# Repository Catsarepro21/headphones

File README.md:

# Headphones

I wanted to make my own over-ear headphones and learn how to fit the audio electronics, battery, and controls into something I could actually wear. I also wanted a fold-up mic and RGB around the cups.

The cups are closed-back and use 40 mm Dayton drivers, an adjustable OKCSC headband, and Brainwavz memory-foam pads. There are 16 LEDs in each cup. The design uses Bluetooth for phone audio, a USB dongle for PC audio and the boom mic, and USB-C for charging and wired SignalRGB. The first physical build still needs testing.

## PCB and schematic

## Files

- [BOM](BOM.md) and [CSV](BOM.csv)
- [Onshape assembly](https://cad.onshape.com/documents/7dd0dda11718de6338e637f2/w/5f67542aa0c734a01c21f813/e/294b57f9c610073ea687bedc) and [STEP files](CAD/)
- [KiCad projects and fabrication files](PCB/fabrication/)
- [Wiring](https://github.com/Catsarepro21/headphones/blob/79efcd8d71c05d15650749ef6cd352ed8c2b8722/PCB/Harness%20wiring.md) and [RGB power](https://github.com/Catsarepro21/headphones/blob/79efcd8d71c05d15650749ef6cd352ed8c2b8722/PCB/LED%20rail%20protection.md)
- [Headset firmware](code/headset/) and [dongle firmware](code/dongle/)
- [SignalRGB plugin](code/signalrgb/Headphones.js)

## How to build it

1. Order the boards from the [fabrication folders](PCB/fabrication/). You need one of each board and two copies of the RGB ring. Check the board thicknesses before ordering.
2. Print the parts from [Onshape](https://cad.onshape.com/documents/7dd0dda11718de6338e637f2/w/5f67542aa0c734a01c21f813/e/294b57f9c610073ea687bedc). Dry-fit the headband, pads, baffles, and battery wiring before committing to the final cup prints. The deeper baffles still need a fit check with the actual battery and thermistor.
3. Solder the boards and run the wires using the [pinout](https://github.com/Catsarepro21/headphones/blob/79efcd8d71c05d15650749ef6cd352ed8c2b8722/PCB/Harness%20wiring.md). The main board has a few parts to leave off, so check the [assembly notes](https://github.com/Catsarepro21/headphones/blob/79efcd8d71c05d15650749ef6cd352ed8c2b8722/PCB/fabrication/README.md#before-assembly) first. Try the BM83 soldering setup on a spare board.
4. Check for shorts and confirm battery polarity before plugging anything in. Start with a current-limited supply and leave the battery and RGB rings disconnected.
5. Flash the [headset](code/headset/) and [dongle](code/dongle/) over SWD. Measure the dongle's reference voltage first and use a probe that supports 1.8 V.
6. Try audio and the flip-up mic in both modes, then check charging and RGB. Make sure your ears clear the grilles when the pads compress before closing up the cups.

## BOM

One build comes to about **$309.35**, including $25 for printing and its shipping and $3 for the selector seal. If you need calipers, add $11.99 for a **$321.34** total. Other shipping, tax, and extra bench tools are separate. [Caliper](https://www.harborfreight.com/painting/measuring-marking/calipers-micrometer/6-in-composite-digital-caliper-63586.html) [Pricing sheet](https://docs.google.com/spreadsheets/d/1EZlvAER-2UgOb8yQGnecRwhJc7PUS93z2gQPCFvvkVY/edit)

| Item | Quantity | Description | Link | Unit price (USD) | Total price (USD) | Notes |
| --- | --- | --- | --- | --- | --- | --- |
| OKCSC 110 mm padded headband | 1 | Adjustable headband and yokes | [Buy](<https://www.aliexpress.us/item/3256810368016901.html>) | $29.00 | $29.00 | 110 mm variant. |
| Brainwavz Oval Micro Suede BWAVZ-OVLBKMS-BAR | 1 | Black foam pair. 110 × 90 × 30 mm, 70 × 50 mm opening. | [Buy](<https://www.brainwavzaudio.com/collections/accessories/products/headphone-memory-foam-earpads-oval-micro-suede>) | $18.55 | $18.55 | Rear mounting flap. |
| Dayton CE38MB-32 drivers | 2 | 40 mm nominal, 32 Ω each | [Buy](<https://www.parts-express.com/Dayton-Audio-CE38MB-32-1-1-2-Mini-Speaker-Black-32-Ohm-285-131>) | $3.49 | $6.98 | Sold individually. |
| Ebyte E73-2G4M08S1C | 2 | 2.4 GHz nRF52840 radio and MCU | [Buy](<https://www.robotshop.com/products/ebyte-e73-2g4m08s1c-iot-solutions-modules-nrf52840-ble50-smd-24ghz-nordic-wireless-module>) | $6.50 | $13.00 | One per board. |
| Microchip BM83SM1-00AB | 1 | Bluetooth Classic and headphone driver | [Buy](<https://www.digikey.com/en/products/detail/microchip-technology/BM83SM1-00AB/12823501>) | $13.18 | $13.18 |  |
| TI TLV320AIC3204IRHBR | 1 | Stereo codec with headphone amplifier | [Buy](<https://www.digikey.com/en/products/detail/texas-instruments/TLV320AIC3204IRHBR/1952545>) | $5.59 | $5.59 |  |
| TI TS5A22362DGSR | 3 | Speaker and mic/bias selection | [Buy](<https://www.lcsc.com/product-detail/Analog-Switches-Multiplexers_Texas-Instruments-TS5A22362DGSR_C201663.html>) | $0.9538 | $2.86 | LCSC part C201663. |
| PUI AOM-4544P-2-R capsules | 2 | One boom mic and one ambient mic | [Buy](<https://www.digikey.com/en/products/detail/pui-audio-inc/AOM-4544P-2-R/1745492>) | $1.48 | $2.96 | One capsule per mic. |
| TI BQ24074RGTR | 1 | 1S 4.20 V charger and power path | [Buy](<https://www.digikey.com/en/products/detail/texas-instruments/BQ24074RGTR/2047269>) | $2.43 | $2.43 | About 500 mA charge. USB starts at 100 mA, then about 390 mA after setup. |
| TI TPS63031DSKR | 1 | 3.3 V buck-boost supply | [Buy](<https://www.lcsc.com/product-detail/dc-dc-converters_texas-instruments-tps63031dskr_C15516.html>) | $1.0429 | $1.04 | LCSC part C15516. |
| Adafruit 2011 protected 1S pack | 1 | 2000 mAh, 3.7 V, 60 × 36 × 7 mm | [Buy](<https://www.digikey.com/en/products/detail/adafruit-industries-llc/2011/6612469>) | $12.50 | $12.50 | Battery for this build. Tray fit pending. |
| Semitec 103AT-2 thermistor | 1 | 10 kΩ at 25 °C, B3435 NTC for charger TS | [Buy](<https://www.digikey.com/en/products/detail/semitec-usa-corp/103at-2/16579059>) | $0.68 | $0.68 | External battery temperature sensor. |
| Adafruit 3814 battery pigtail | 1 | 2-pin JST-PH mating adapter for the 2011 | [Buy](<https://www.digikey.com/en/products/detail/adafruit-industries-llc/3814/9380221>) | $0.75 | $0.75 | Mates with the battery’s original plug. |
| TI TPS61023DRLR | 1 | 5 V boost for both RGB rings | [Buy](<https://www.digikey.com/en/products/detail/texas-instruments/TPS61023DRLR/11310629>) | $1.38 | $1.38 | U5 makes 5 V for the rings. 300 mA LED budget. |
| TI TPS2553DBVR-1 | 1 | U13 hardware cutoff for both LED rings | [Buy](<https://www.digikey.com/en/products/detail/texas-instruments/TPS2553DBVR-1/2047901>) | $1.06 | $1.06 | -1 latch-off version, SOT-23-6. R210 sets the limit. |
| 68.1 kΩ 0603 · Yageo RC0603FR-0768K1L | 1 | R210 sets the LED cutoff threshold | [Buy](<https://www.digikey.com/en/products/detail/yageo/RC0603FR-0768K1L/727354>) | $0.10 | $0.10 | 1%. Expected trip at 0.34–0.44 A. |
| TI SN74AHCT1G125DBVR | 1 | 3.3 V to 5 V RGB data buffer | [Buy](<https://www.digikey.com/en/products/detail/texas-instruments/SN74AHCT1G125DBVR/376028>) | $0.14 | $0.14 |  |
| TI TLV803EA29DBZR | 1 | BM83 2.93 V open-drain reset supervisor | [Buy](<https://www.digikey.com/en/products/detail/texas-instruments/TLV803EA29DBZR/11308855>) | $0.50 | $0.50 |  |
| Bourns SRN4018-1R5Y | 1 | 1.5 µH inductor for 3.3 V supply | [Buy](<https://www.digikey.com/en/products/detail/bourns-inc/SRN4018-1R5Y/3821618>) | $0.37 | $0.37 |  |
| Bourns SRN6045TA-1R0Y | 1 | 1.0 µH inductor for 5 V boost | [Buy](<https://www.digikey.com/en/products/detail/bourns-inc/SRN6045TA-1R0Y/6155099>) | $0.46 | $0.46 |  |
| Kyocera KC3225K12.2880C1GE00 | 1 | 12.288 MHz, 3.3 V codec master clock (Y1) | [Buy](<https://www.digikey.com/en/products/detail/kyocera-avx/KC3225K12-2880C1GE00/5322447>) | $1.39 | $1.39 | Cut tape. C212 bypass. |
| Amphenol 12401610E4#2A | 1 | USB-C headset receptacle | [Buy](<https://www.digikey.com/en/products/detail/amphenol-icc-commercial-products/12401610E4-2A/5775520>) | $1.43 | $1.43 |  |
| ST USBLC6-2SC6 | 1 | Headset USB data ESD array | [Buy](<https://www.digikey.com/en/products/detail/stmicroelectronics/USBLC6-2SC6/1040559>) | $0.54 | $0.54 |  |
| Nexperia PESD5V0U2BT-QR | 1 | Dongle USB D+ and D− ESD protection | [Buy](<https://www.digikey.com/en/products/detail/nexperia-usa-inc/PESD5V0U2BT-QR/17296191>) | $0.31 | $0.31 | Dongle D1 goes on the bottom (SOT-23). |
| Molex 1054440011 | 1 | Right-angle USB-C dongle plug | [Buy](<https://www.digikey.com/en/products/detail/molex/1054440011/6173183>) | $3.10 | $3.10 |  |
| Amphenol 10165794-Z0100YBLF USB-C cable | 1 | 1 m black USB-C to USB-C. USB 2.0 data and 5 V charging. | [Buy](<https://www.digikey.com/en/products/detail/amphenol-cs-fci/10165794-Z0100YBLF/22527932>) | $4.67 | $4.67 | Max plug body is 11.2 × 6.7 mm. Fits the 14.5 × 8.0 mm CAD opening. |
| Worldsemi WS2812B-B/W | 35 | Buy 35 to populate 32 pixels | [Buy](<https://www.lcsc.com/product-detail/C114586.html>) | $0.1042 | $3.65 | 32 LEDs used, 3 spare. |
| E-Switch TL3342F260QG | 5 | Four earcup controls and one main board reset switch | [Buy](<https://www.digikey.com/en/products/detail/e-switch/TL3342F260QG/6596498>) | $0.62 | $3.10 | Play/pause, volume +/−, pair, and mainboard reset. |
| C&K JS102011SAQN | 1 | Two-position Bluetooth/dongle selector | [Buy](<https://www.digikey.com/en/products/detail/c-k/JS102011SAQN/1640095>) | $0.90 | $0.90 | 2 mm travel. 1.0 mm selector PCB. |
| C&K 1101M1S3ZQE2 master power switch | 1 | Maintained slide switch connects main SW1 VSYS to SYS_SW | [Buy](<https://www.digikey.com/en/products/detail/c-k/1101M1S3ZQE2/67048>) | $8.05 | $8.05 | 6 A resistive at 28 VDC. Onshape M1. |
| Aratas / Omron B3F-1000 boom mute switch | 1 | 6 × 6 mm normally-open through-hole tact. Boom cam holds contact closed when deployed. | [Buy](<https://www.digikey.com/en/products/detail/aratas-formerly-omron-components/B3F-1000/33150>) | $0.35 | $0.35 | Mute switch on SW7 pads 1–2. Boom mic on J7. |
| Sullins PEC36SAAN 2.54 mm headers | 1 | 36-pin breakaway strip for the service headers | [Buy](<https://www.digikey.com/en/products/detail/sullins-connector-solutions/PEC36SAAN/859153>) | $1.44 | $1.44 | 8 pins used for J2 and J4. |
| Adafruit 5087 3-pin inline disconnect | 1 | Matched JST-PH-compatible 26 AWG pigtail pair | [Buy](<https://www.digikey.com/en/products/detail/adafruit-industries-llc/5087/14652853>) | $0.95 | $0.95 | Matched pair for the battery and temp sensor. |
| Qualtek Q2-Z-RK1-3/32-01-6IN-32 | 1 | 3/32 in black 2:1 heat shrink | [Buy](<https://www.digikey.com/en/products/detail/qualtek/Q2-Z-RK1-3-32-01-6IN-32/1210238>) | $1.38 | $1.38 | For small splices. |
| Qualtek Q2-Z-RK1-1/8-01-6IN-28 | 1 | 1/8 in black 2:1 heat shrink | [Buy](<https://www.digikey.com/en/products/detail/qualtek/Q2-Z-RK1-1-8-01-6IN-28/1210237>) | $1.52 | $1.52 | For thicker splices. |
| Qualtek Q2-Z-RK1-3/16-01-6IN-24 | 1 | 3/16 in black 2:1 heat shrink | [Buy](<https://www.digikey.com/en/products/detail/qualtek/Q2-Z-RK1-3-16-01-6IN-24/1210246>) | $1.59 | $1.59 | For larger lugs. |
| Adafruit 3892 flexible headband wire | 3 | Black stranded silicone 26 AWG. Each pack has four separate 1 m conductors. | [Buy](<https://www.digikey.com/en/products/detail/adafruit-industries-llc/3892/9603618>) | $1.95 | $5.85 | 9 wires through the headband. Ø1.5 ±0.1 mm each. |
| Lite-On LTST-C170KGKT | 1 | Dongle status indication | [Buy](<https://www.digikey.com/en/products/detail/liteon/LTST-C170KGKT/386776>) | $0.19 | $0.19 |  |
| 100 nF 0805 · Würth 885012207098R | 50 | Bypass | [Buy](<https://www.digikey.com/en/products/detail/w%C3%BCrth-elektronik/885012207098R/21719484>) | $0.0302 | $1.51 | 49 used. |
| 100 pF 0805 · KEMET C0805C101J5GACTU | 2 | Capacitors C27 and C29 | [Buy](<https://www.digikey.com/en/products/detail/kemet/C0805C101J5GACTU/411397>) | $0.19 | $0.38 | C0G, 50 V, ±5%. |
| 220 pF 0805 · KEMET C0805C221J5GACTU | 1 | Feed-forward capacitor across the RGB boost feedback upper resistor | [Buy](<https://www.digikey.com/en/products/detail/kemet/C0805C221J5GACTU/411402>) | $0.20 | $0.20 | C31. C0G, 50 V, ±5%. |
| 1 µF 0805 · Samsung CL21B105KOFNFNE | 10 | Coupling and bypass | [Buy](<https://www.digikey.com/en/products/detail/samsung-electro-mechanics/CL21B105KOFNFNE/3891016>) | $0.0590 | $0.59 | 7 used, 3 spare. |
| Murata GRM1885C1H103JA01J | 1 | 10 nF C0G 0603 bypass for the 12.288 MHz clock | [Buy](<https://www.digikey.com/en/products/detail/murata-electronics/GRM1885C1H103JA01J/4905215>) | $0.1300 | $0.13 | Main C212 next to Y1. 50 V, ±5%. |
| 1 µF 0603 · Yageo CC0603KRX7R7BB105 | 2 | C211 BM83 mic-bias bypass and C213 LED protection switch bypass | [Buy](<https://www.digikey.com/en/products/detail/yageo/CC0603KRX7R7BB105/2833611>) | $0.24 | $0.48 | X7R, 16 V, ±10%, 0603. |
| 4.7 µF 0805 · Samsung CL21B475KAFNNNE | 2 | Main charger input and dongle USB VBUS/VDDH bypass | [Buy](<https://www.digikey.com/en/products/detail/samsung-electro-mechanics/CL21B475KAFNNNE/3888627>) | $0.50 | $1.00 | 25 V X7R. Main C1 and dongle C1. |
| 10 µF 0805 · Samsung CL21B106KOQNNNE | 13 | Supply bypass and stabilization, 12 main and one dongle | [Buy](<https://www.digikey.com/en/products/detail/samsung-electro-mechanics/CL21B106KOQNNNE/3890958>) | $0.165 | $2.15 | Dongle C2 on VDD. X7R, 16 V, ±10%, 1.40 mm max. |
| 22 µF 0805 · Samsung CL21A226MPQNNNE | 3 | Boost and BM83 supply bypass | [Buy](<https://www.digikey.com/en/products/detail/samsung-electro-mechanics/CL21A226MPQNNNE/3888568>) | $0.19 | $0.57 | 10 V X5R. |
| 47 µF · Nichicon UWT1V470MCL1GS | 2 | One bulk capacitor on each LED ring | [Buy](<https://www.digikey.com/en/products/detail/nichicon/UWT1V470MCL1GS/589943>) | $0.44 | $0.88 | One C52 per ring. 35 V, ±20%, Ø6.3 × 5.8 mm. |
| 220 µF · Nichicon UWT0J221MCL6GS | 2 | Codec headphone DC blocking | [Buy](<https://www.digikey.com/en/products/detail/nichicon/UWT0J221MCL6GS/2550846>) | $0.39 | $0.78 | C24, C25. |
| 33 Ω 0805 · RC0805FR-0733RL | 10 | RGB/UART series | [Buy](<https://www.digikey.com/en/products/detail/yageo/RC0805FR-0733RL/730809>) | $0.0340 | $0.34 | 5 used. |
| 330 Ω 0805 · RC0805FR-07330RL | 2 | RGB data series | [Buy](<https://www.digikey.com/en/products/detail/yageo/RC0805FR-07330RL/727866>) | $0.10 | $0.20 |  |
| 1 kΩ 0805 · RC0805FR-071KL | 1 | Dongle status LED | [Buy](<https://www.digikey.com/en/products/detail/yageo/RC0805FR-071KL/727444>) | $0.10 | $0.10 | Dongle R5. |
| 1.78 kΩ 0805 · CRCW08051K78FKEA | 1 | Charge programming | [Buy](<https://www.digikey.com/en/products/detail/vishay-dale/CRCW08051K78FKEA/1175663>) | $0.10 | $0.10 | R1. |
| 2.2 kΩ 0805 · RC0805FR-072K2L | 2 | Electret bias | [Buy](<https://www.digikey.com/en/products/detail/yageo/RC0805FR-072K2L/727676>) | $0.10 | $0.20 | R18 and R19. |
| 3.92 kΩ 0805 · RC0805FR-073K92L | 1 | Main R2 charger input-current limit | [Buy](<https://www.digikey.com/en/products/detail/yageo/RC0805FR-073K92L/727840>) | $0.10 | $0.10 | 1%. Sets the configured USB input limit. R1 sets charge current. |
| 4.7 kΩ 0805 · RC0805FR-074K7L | 3 | Digital pull-up and bias | [Buy](<https://www.digikey.com/en/products/detail/yageo/RC0805FR-074K7L/727929>) | $0.10 | $0.30 |  |
| 5.1 kΩ 0805 · CRCW08055K10FKEA | 3 | USB-C CC terminations | [Buy](<https://www.digikey.com/en/products/detail/vishay-dale/CRCW08055K10FKEA/1180863>) | $0.10 | $0.30 | USB-C CC. |
| 10 kΩ 0805 · RC0805FR-0710KL | 10 | Bias and pull resistors | [Buy](<https://www.digikey.com/en/products/detail/yageo/RC0805FR-0710KL/727535>) | $0.0340 | $0.34 | 5 used. |
| 46.4 kΩ 0805 · RC0805FR-0746K4L | 1 | Charger timer programming | [Buy](<https://www.digikey.com/en/products/detail/yageo/RC0805FR-0746K4L/727969>) | $0.10 | $0.10 | R3. |
| 100 kΩ 0805 · Yageo RC0805FR-07100KL | 10 | Mode and other pull resistors | [Buy](<https://www.digikey.com/en/products/detail/yageo/RC0805FR-07100KL/730491>) | $0.0360 | $0.36 | 8 used. |
| 732 kΩ 0805 · RC0805FR-07732KL | 1 | Boost feedback | [Buy](<https://www.digikey.com/en/products/detail/yageo/RC0805FR-07732KL/728131>) | $0.10 | $0.10 | R22. |
| 56 kΩ 0805 · Yageo RC0805FR-0756KL | 1 | Main R10 lower battery-sense resistor | [Buy](<https://www.digikey.com/en/products/detail/yageo/RC0805FR-0756KL/728033>) | $0.10 | $0.10 | 1%. |
| 1 MΩ 0805 · RC0805FR-071ML | 1 | Main R9 upper battery-sense resistor | [Buy](<https://www.digikey.com/en/products/detail/yageo/RC0805FR-071ML/727445>) | $0.10 | $0.10 | R9 = 1 MΩ, R10 = 56 kΩ. At 4.2 V, ADC stays below 0.23 V with 1% parts. |
| DoonX 0.4 mm black silicone sheet | 1 | Selector seal stock | [Buy](<https://www.doonx.com/products/0-4mm-black-silicone-rubber-sheet>) | $3.00 | $3.00 | $3 estimate for the cut sheet. |
| ServoCity 2929-0216-0352 silicone sheet | 1 | 216 × 352 mm, 1 mm thick, 30A, adhesive backed | [Buy](<https://www.servocity.com/adhesive-backed-silicone-rubber-sheet-30a-durometer-1mm-thickness-216mm-x-352mm/>) | $11.99 | $11.99 | Baffle gasket material. |
| Kunin 893818 black 1 mm polyester felt | 1 | Matched left and right damping samples | [Buy](<https://www.hobbylobby.com/fabric-sewing/craft-fabrics/felt-fabric-sheets/black---felt-sheet---1mm/p/80957611>) | $0.25 | $0.25 | One 9 × 12 in sheet for both cups. |
| CNC Kitchen TC-M2x3.0 insert pack | 1 | M2 × 3 heat-set insert kit | [Buy](<https://cnckitchenus.store/products/heat-set-insert-m2-x-3-100-pieces>) | $11.50 | $11.50 | 100 per pack. |
| Olander .2C5SHCS M2 × 5 screws | 5 | M2 × 0.4 DIN 912 stainless socket cap | [Buy](<https://www.olander.com/items/.2C5SHCS>) | $0.213 | $1.07 | 2 for the selector, 1 for the boom guard, 2 for the power slide. |
| Olander .2CHNTS M2 hex nuts | 2 | Stainless M2 × 0.4, 4 mm AF, 1.60 mm max thick | [Buy](<https://www.olander.com/items/.2CHNTS>) | $0.095 | $0.19 | For the power slide. |
| Panduit PLT1M-M300 black nylon ties | 3 | Cable strain relief and connector shelf retention | [Buy](<https://www.digikey.com/en/products/detail/panduit-corp/PLT1M-M300/451182>) | $0.12 | $0.36 | 99.06 × 2.50 mm. Two for the bridge, one for the connector shelf. |
| 8858 110 V hot-air station | 1 | 110 V station with adjustable temperature and airflow | [Buy](<https://www.ebay.com/itm/157518504793>) | $29.99 | $29.99 | For soldering the mainboard. |
| All 3D-printed parts and printing | 1 | Matte-black closed-back cups, mounts and dongle case | [Request](<https://printlegion.hackclub.com/docs/requesters>) | $25.00 | $25.00 | Provisional $25. About 300 g of filament plus print shipping. |
| Custom PCB fabrication | 1 | One lot of six PCB designs, five bare copies each | [Order](<https://cart.jlcpcb.com/quote>) | $38.70 | $38.70 | Estimate before shipping. Seven boards go into the build. |
| Chip Quik NC191SNL15 solder paste | 1 | No-clean SAC305 solder paste, 15 g syringe | [Buy](<https://www.chipquik.com/store/product_info.php?products_id=473017>) | $12.95 | $12.95 | For hot-air reflow. |
| PCB solder stencils | 1 | Three patterns for main top, main bottom, and RGB rings | [Order](<https://cart.jlcpcb.com/quote?orderType=1&stencil=true>) | $9.00 | $9.00 | Estimated at $3 per stencil. |

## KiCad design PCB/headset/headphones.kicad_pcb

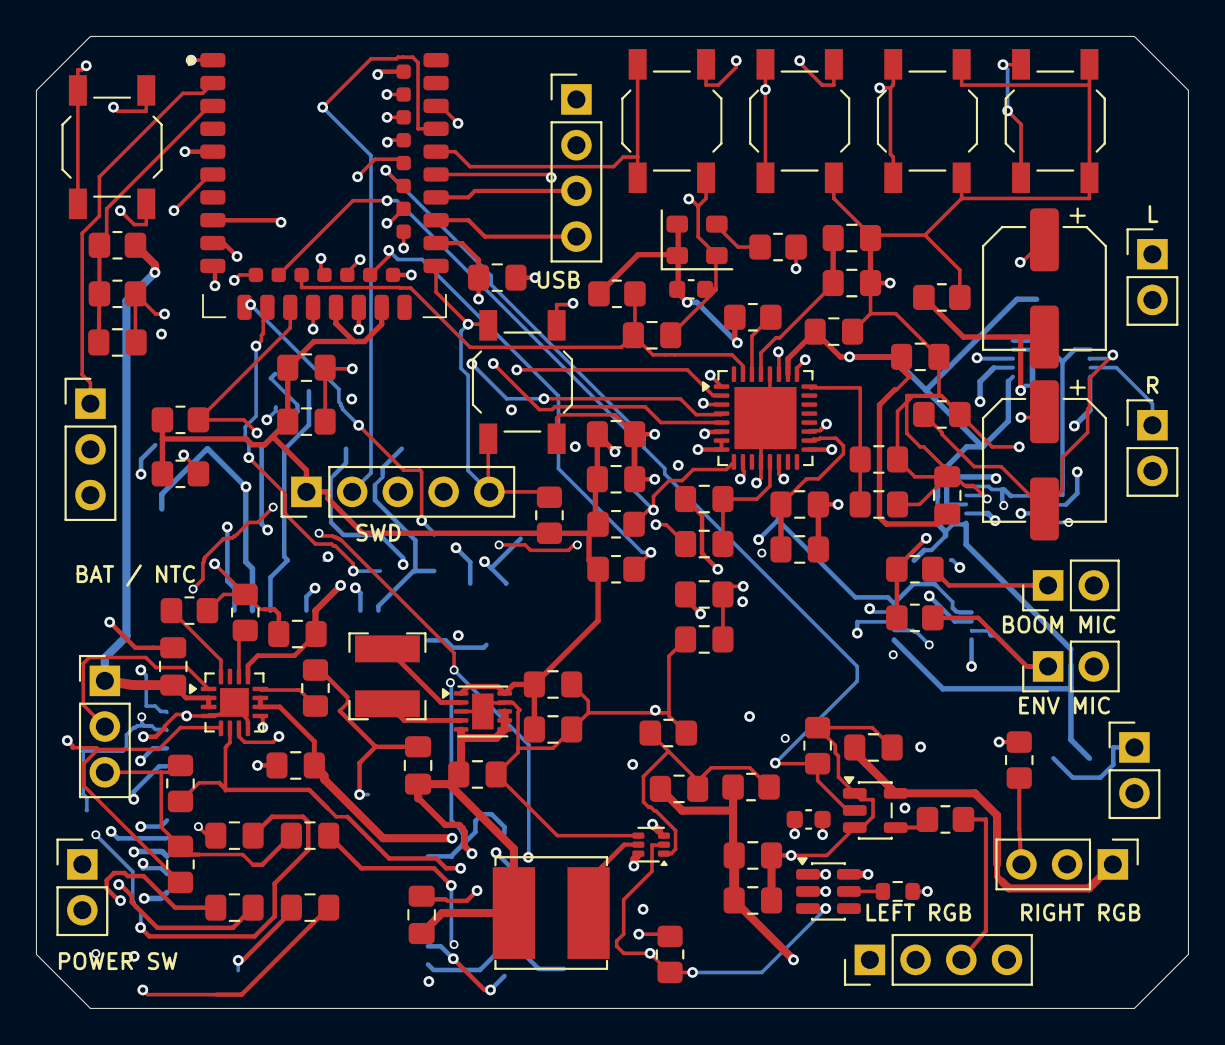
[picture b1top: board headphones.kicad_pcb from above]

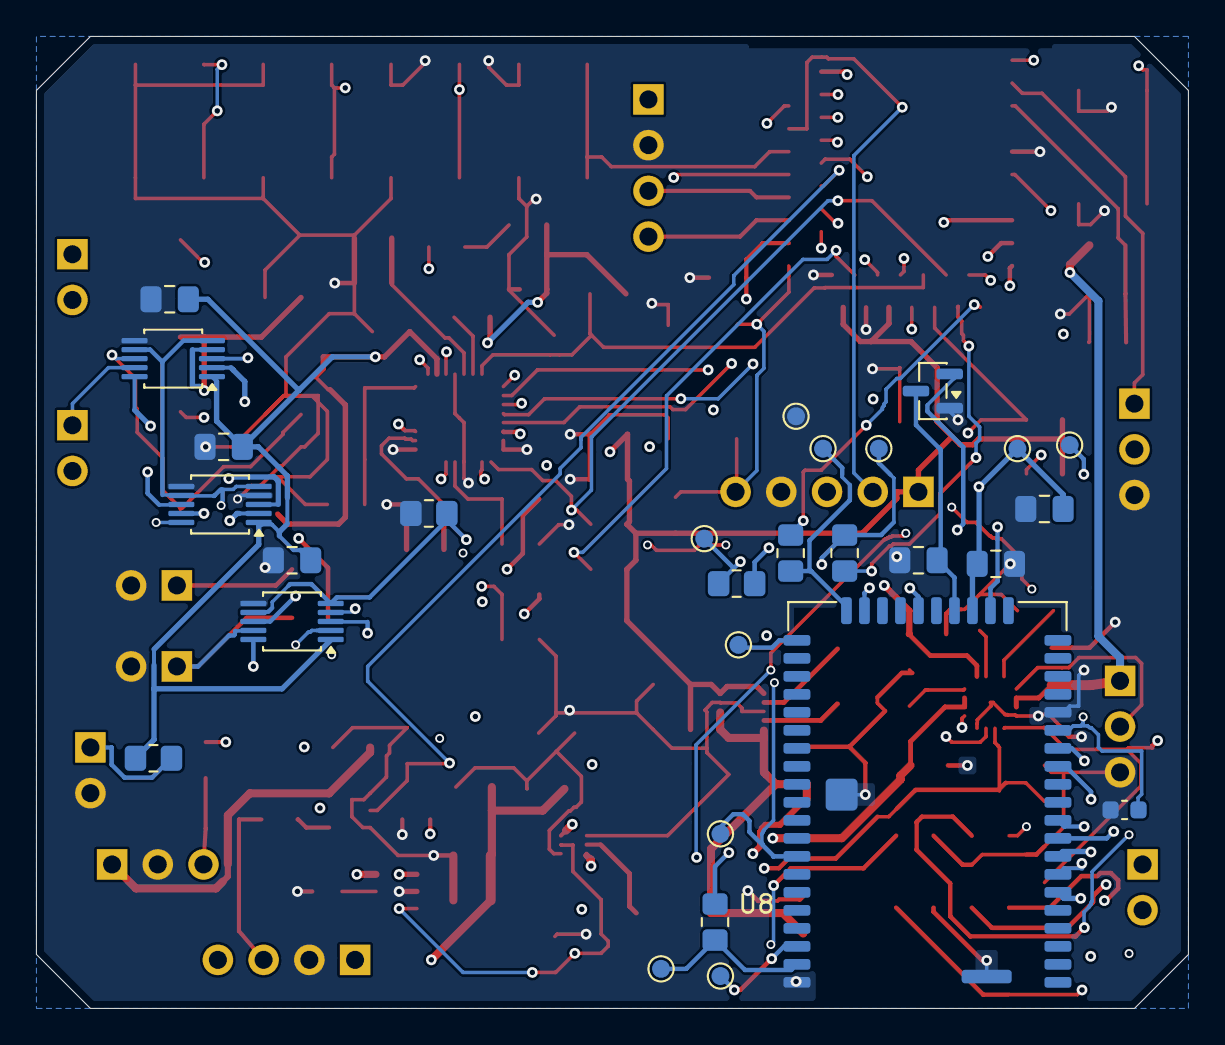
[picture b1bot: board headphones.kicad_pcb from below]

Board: 4 copper layers, 64.0 x 54.0 mm, 122 parts (28 on the bottom side), 93 nets.

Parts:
C1: 4.7u; C_0805_2012Metric_Pad1.18x1.45mm_HandSolder
C2, C3, C4, C6, C7, C8, C14, C16, C18, C20, C22, C32: 10u; C_0805_2012Metric_Pad1.18x1.45mm_HandSolder
C5, C9, C11, C12, C13, C15, C17, C19, C21, C23, C35, C202, C203, C208, C209, C210: 100n; C_0805_2012Metric_Pad1.18x1.45mm_HandSolder
C10, C26, C28, C204, C205, C206, C207: 1u; C_0805_2012Metric_Pad1.18x1.45mm_HandSolder
C24, C25: 220u; CP_Elec_6.3x7.7
C27, C29: 100p; C_0805_2012Metric_Pad1.18x1.45mm_HandSolder
C31: 220p; C_0805_2012Metric_Pad1.18x1.45mm_HandSolder
C33, C34, C201: 22u; C_0805_2012Metric_Pad1.18x1.45mm_HandSolder
C211, C213: 1u; C_0603_1608Metric
C212: 10n; C_0603_1608Metric
J1, J4, J11: Conn_01x03; PinHeader_1x03_P2.54mm_Vertical
J2: Conn_01x05; PinHeader_1x05_P2.54mm_Vertical
J3, J10: Conn_01x04; PinHeader_1x04_P2.54mm_Vertical
J5, J6, J7, J8: Conn_01x02; PinHeader_1x02_P2.54mm_Vertical
L1: 1.5uH; L_Bourns-SRN4018
L2: 1uH; L_Bourns_SRN6045TA
R1: 1.78k; R_0805_2012Metric_Pad1.20x1.40mm_HandSolder
R2: 3.92k; R_0805_2012Metric_Pad1.20x1.40mm_HandSolder
R3: 46.4k; R_0805_2012Metric_Pad1.20x1.40mm_HandSolder
R4, R5, R16, R17, R23, R24, R25, R32: 100k; R_0805_2012Metric_Pad1.20x1.40mm_HandSolder
R6, R7, R8, R14, R33: 10k; R_0805_2012Metric_Pad1.20x1.40mm_HandSolder
R9: 1M; R_0805_2012Metric_Pad1.20x1.40mm_HandSolder
R10: 56k; R_0805_2012Metric_Pad1.20x1.40mm_HandSolder
R11, R12, R13: 4.7k; R_0805_2012Metric_Pad1.20x1.40mm_HandSolder
R15, R28, R29, R30, R31: 33R; R_0805_2012Metric_Pad1.20x1.40mm_HandSolder
R18, R19: 2.2k; R_0805_2012Metric_Pad1.20x1.40mm_HandSolder
R22: 732k; R_0805_2012Metric_Pad1.20x1.40mm_HandSolder
R26, R27: 330R; R_0805_2012Metric_Pad1.20x1.40mm_HandSolder
R210: 68.1k; R_0603_1608Metric
SW1: SW_SPST; PinHeader_1x02_P2.54mm_Vertical
SW2, SW3, SW4, SW5, SW6, SW7: SW_Push; SW_SPST_TL3342
SW8: BT / Dongle; PinHeader_1x02_P2.54mm_Vertical
TP1: BT_RXD; TestPoint_Pad_D1.0mm
TP2: BT_TXD; TestPoint_Pad_D1.0mm
TP3: BT_MFB; TestPoint_Pad_D1.0mm
TP4: BT_SYS_CFG; TestPoint_Pad_D1.0mm
TP5: BT_RESET_N; TestPoint_Pad_D1.0mm
TP6: GND; TestPoint_Pad_D1.0mm
TP7: BT_UART_CTS; TestPoint_Pad_D1.0mm
TP8: +3V3; TestPoint_Pad_D1.0mm
TP9: BT_TX_IND; TestPoint_Pad_D1.0mm
TP10: BT_ADAP_IN; TestPoint_Pad_D1.0mm
U1: E73-2G4M08S1C; nRF52840_E73-2G4M08S1C
U2: BQ24074RGT; VQFN-16-1EP_3x3mm_P0.5mm_EP1.6x1.6mm
U3: TPS63031DSK; WSON-10-1EP_2.5x2.5mm_P0.5mm_EP1.2x2mm
U4: TLV320AIC3204IRHBR; Texas_RHB0032E_VQFN-32-1EP_5x5mm_P0.5mm_EP3.45x3.45mm
U5: TPS61023DRLR; SOT-563
U6: SN74AHCT1G125DBVR; SOT-23-5
U8: BM83SM1-00AB; Microchip_BM83_GroundEscape
U9, U10, U11: TS5A22362DGSR; TSSOP-10_3x3mm_P0.5mm
U12: TLV803EA29DBZR; SOT-23
U13: TPS2553DBVR-1; SOT-23-6
Y1: KC3225K12.2880C1GE00; Oscillator_Kyocera_KC3225K

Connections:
+3V3: C6.1, C7.1, C8.1, C9.1, C13.1, C14.1, C15.1, C16.1, C17.1, C201.1, C202.1, C208.1, C209.1, C210.1, C212.1, J2.1, R6.1, R7.1, R8.1, R11.1, R12.1, R13.1, R14.1, R33.2, TP8.1, U1.19, U1.23, U3.1, U3.10, U4.6, U4.26, U8.23, U9.1, U10.1, U11.1, Y1.1, Y1.4
+5V_RGB: C35.1, J10.1, J11.1, U6.5, U13.6
+5V_RGB_RAW: C31.1, C33.1, C34.1, C213.1, R22.1, U5.6, U13.1
/AUDIO_ADC: U1.30, U4.5
/AUDIO_BCLK: U1.20, U4.2
/AUDIO_DAC: U1.28, U4.4
/AUDIO_LRCLK: U1.33, U4.3
/BOOM_IN: C26.2, C27.1, U4.13
/BTN_PAIR: SW6.1, U1.40
/BT_ADAP_IN: TP10.1, U8.22
/BT_AUDIO_SEL: R32.1, U1.9, U9.5, U9.7, U10.5, U10.7, U11.5, U11.7
/BT_HP_COM: U8.7, U10.2
/BT_HP_L: U8.8, U9.2
/BT_HP_R: U8.6, U9.10
/BT_MFB: R30.2, TP3.1, U8.26
/BT_MICBIAS: C211.1, U8.15, U10.10
/BT_MIC_AMBIENT_AC: C206.1, U11.10
/BT_MIC_BOOM_AC: C204.1, U11.2
/BT_MIC_N1: C205.2, U8.13
/BT_MIC_N2: C207.2, U8.9
/BT_MIC_P1: C204.2, U8.14
/BT_MIC_P2: C206.2, U8.10
/BT_MODE_N: R33.1, SW8.1, U1.8
/BT_RESET_N: TP5.1, U8.43, U12.2
/BT_RXD: R28.2, TP1.1, U8.29
/BT_SYS_CFG: TP4.1, U8.31
/BT_SYS_PWR: C203.1, U8.24, U12.3
/BT_TXD: R29.1, TP2.1, U8.30
/BT_TX_IND: R31.1, TP9.1, U8.49
/BT_UART_CTS: TP7.1, U8.48
/CHG_N: R7.2, U1.18, U2.9
/CODEC_HP_L: C24.2, R16.1, U9.4
/CODEC_HP_R: C25.2, R17.1, U9.8
/CODEC_MIC_AMBIENT: C28.1, U11.8
/CODEC_MIC_BOOM: C26.1, U11.4
/CODEC_RESET_N: C12.1, R14.2, U1.16, U4.31
/DRV_L: J5.1, U9.3
/DRV_R: J6.1, U9.9
/DRV_RETURN: J5.2, J6.2, U10.3
/ENV_IN: C28.2, C29.1, U4.14
/HOST_BT_MFB: R30.1, U1.42
/HOST_BT_RX: R29.2, U1.11
/HOST_BT_TX: R28.1, U1.13
/HOST_BT_WAKE: R31.2, U1.10
/HPL: C24.1, U4.25
/HPR: C25.1, U4.27
/I2C_SCL: R11.2, U1.14, U4.9
/I2C_SDA: R12.2, U1.22, U4.10
/MICBIAS: U4.19, U10.8
/MIC_AMBIENT: J8.1, R19.2, U11.9
/MIC_BIAS_SW: R18.1, R19.1, U10.9
/MIC_BOOM: J7.1, R18.2, U11.3
/PGOOD_N: R6.2, U1.15, U2.7
/RGB_DATA: R25.1, U1.32, U6.2
/RGB_ENABLE: R24.1, U1.34, U5.2, U13.3
/RGB_ILIM: R210.1, U13.5
/RGB_LEFT_IN: J10.3, R26.2
/RGB_LEFT_OUT: J10.4, R27.1
/RGB_RIGHT_IN: J11.3, R27.2
/USB_DM: J3.4, U1.29
/USB_DP: J3.3, U1.31
/USB_EN1: R4.1, U1.12, U2.6
/USB_EN2: R5.1, U1.6, U2.5
GND: C1.2, C2.2, C3.2, C4.2, C5.2, C6.2, C7.2, C8.2, C9.2, C10.2, C11.2, C12.2, C13.2, C14.2, C15.2, C16.2, C17.2, C18.2, C19.2, C20.2, C21.2, C22.2, C23.2, C27.2, C29.2, C32.2, C33.2, C34.2, C35.2, C201.2, C202.2, C203.2, C205.1, C207.1, C208.2, C209.2, C210.2, C211.2, C212.2, C213.2, J1.3, J2.4, J3.2, J4.3, J7.2, J8.2, J10.2, J11.2, R1.2, R2.2, R3.2, R4.2, R5.2, R10.2, R16.2, R17.2, R23.2, R24.2, R25.2, R32.2, R210.2, SW2.2, SW3.2, SW4.2, SW5.2, SW6.2, SW7.2, SW8.2, TP6.1, U1.5, U1.21, U1.24, U2.4, U2.8, U2.17, U3.3, U3.9, U3.11, U4.7, U4.8, U4.12, U4.17, U4.28, U4.33, U5.4, U6.1, U6.3, U8.16, U8.50, U8.56, U8.57, U9.6, U10.4, U10.6, U11.6, U12.1, U13.2, Y1.2
unnamed: C11.1, R9.2, R10.1, U1.3
unnamed: J2.5, R8.2, SW2.1, U1.26
unnamed: SW3.1, U1.35
unnamed: SW4.1, U1.36
unnamed: SW5.1, U1.38
unnamed: J4.2, U1.17
unnamed: J4.1, U1.2
unnamed: SW7.1, U1.1
unnamed: J2.3, U1.39
unnamed: J2.2, U1.37
unnamed: R2.1, U2.12
unnamed: R1.1, U2.16
unnamed: R3.1, U2.14
unnamed: J1.2, U2.1
unnamed: L1.1, U3.4
unnamed: L1.2, U3.2
unnamed: C20.1, C21.1, U4.24
unnamed: C18.1, C19.1, U4.29
unnamed: R13.2, U4.30
unnamed: R15.2, U4.1
unnamed: C22.1, C23.1, U4.18
unnamed: C31.2, R22.2, R23.1, U5.1
unnamed: L2.2, U5.5
unnamed: R26.1, U6.4
unnamed: R15.1, Y1.3
PACK_P: C2.1, J1.1, R9.1, U2.2, U2.3
SYS_SW: C4.1, C5.1, C32.1, L2.1, SW1.2, U3.5, U3.6, U3.7, U3.8, U5.3
USB_5V: C1.1, C10.1, J3.1, U1.27, U2.13
VSYS: C3.1, SW1.1, U2.10, U2.11

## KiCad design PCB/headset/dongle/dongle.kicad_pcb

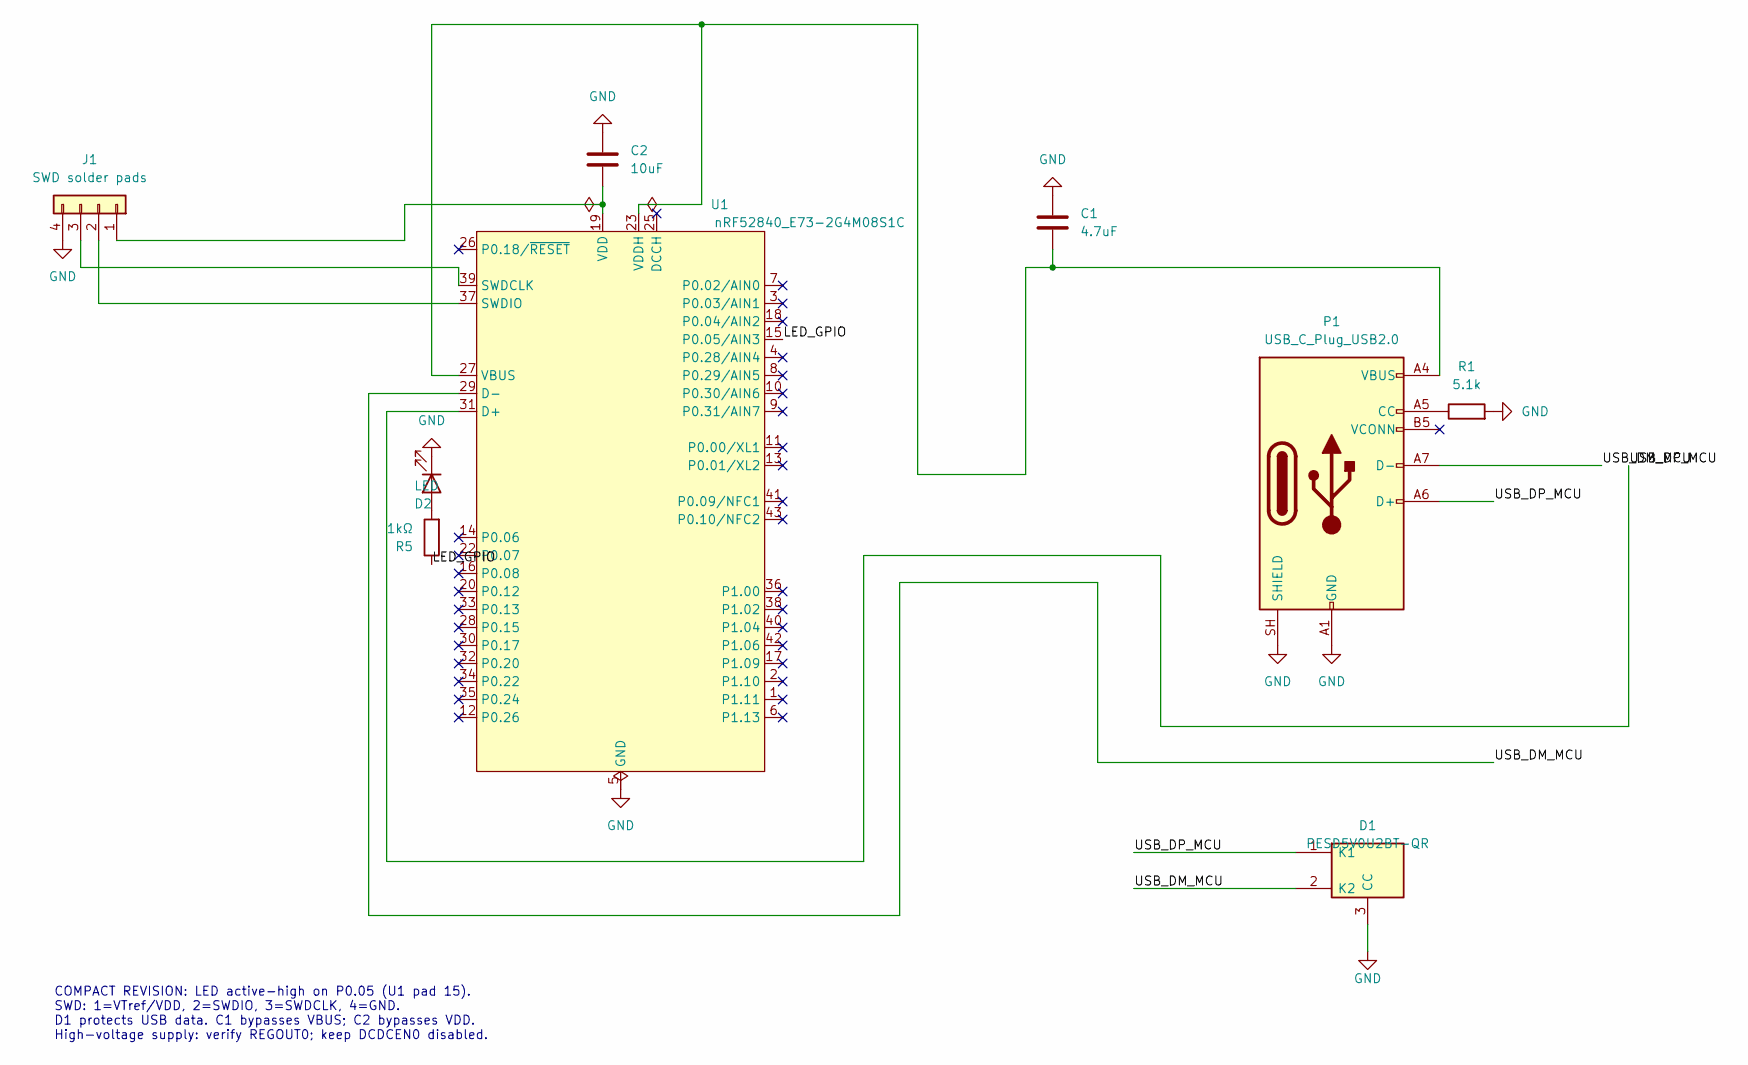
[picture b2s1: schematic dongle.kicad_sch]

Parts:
C1: 4.7uF; C_0805_2012Metric_Pad1.18x1.45mm_HandSolder
C2: 10uF; C_0805_2012Metric_Pad1.18x1.45mm_HandSolder
D1: PESD5V0U2BT-QR; SOT-23
D2: LED; LED_0805_2012Metric_Pad1.15x1.40mm_HandSolder
J1: SWD solder pads; SWD_2x02_P2.54_SolderPads
P1: USB_C_Plug_USB2.0; USB_C_Plug_Molex_105444
R1: 5.1k; R_0805_2012Metric_Pad1.20x1.40mm_HandSolder
R5: 1kΩ; R_0805_2012Metric_Pad1.20x1.40mm_HandSolder
U1: nRF52840_E73-2G4M08S1C; LCSC C356849

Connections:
/LED_GPIO: R5.1, U1.15 (P0.05/AIN3)
/USB_DM_MCU: D1.2 (K2), P1.A7 (D-), U1.29 (D-)
/USB_DP_MCU: D1.1 (K1), P1.A6 (D+), U1.31 (D+)
GND: C1.2, C2.1, D1.3 (CC), D2.1 (K), J1.4, P1.A1 (GND), P1.A12 (GND), P1.B1 (GND), P1.B12 (GND), P1.SH (SHIELD), R1.2, U1.5 (GND), U1.21 (GND), U1.24 (GND)
unnamed: D2.2 (A), R5.2
unnamed: C2.2, J1.1, U1.19 (VDD)
unnamed: J1.2, U1.37 (SWDIO)
unnamed: J1.3, U1.39 (SWDCLK)
unnamed: P1.A5 (CC), R1.1
unnamed: C1.1, P1.A4 (VBUS), P1.A9 (VBUS), P1.B4 (VBUS), P1.B9 (VBUS), U1.23 (VDDH), U1.27 (VBUS)

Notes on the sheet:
COMPACT REVISION: LED active-high on P0.05 (U1 pad 15). SWD: 1=VTref/VDD, 2=SWDIO, 3=SWDCLK, 4=GND. D1 protects USB data. C1 bypasses VBUS; C2 bypasses VDD. High-voltage supply: verify REGOUT0; keep DCDCEN0 disabled.

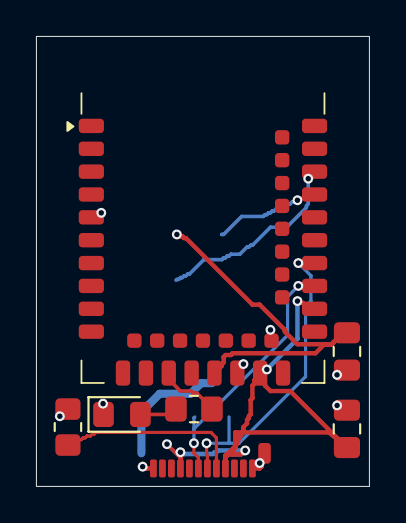
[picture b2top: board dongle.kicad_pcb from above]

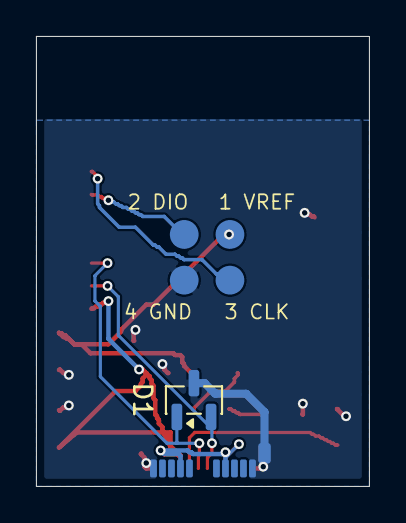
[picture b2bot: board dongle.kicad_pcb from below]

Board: 2 copper layers, 18.5 x 25.0 mm, 9 parts (2 on the bottom side), 10 nets.

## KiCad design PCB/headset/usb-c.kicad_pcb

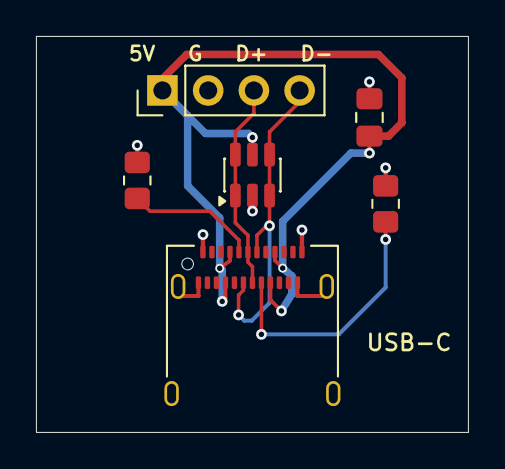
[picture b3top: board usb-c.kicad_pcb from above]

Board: 2 copper layers, 24.0 x 22.0 mm, 6 parts (0 on the bottom side), 6 nets.

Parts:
C30: 100n; C_0805_2012Metric_Pad1.18x1.45mm_HandSolder
J9: Conn_01x04; PinHeader_1x04_P2.54mm_Vertical
J100: USB_C; USB_C_Receptacle_Amphenol_12401610E4-2A
R20, R21: 5.1k; R_0805_2012Metric_Pad1.20x1.40mm_HandSolder
U7: USBLC6-2SC6; SOT-23-6

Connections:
/USB_DM: J9.4, J100.A7, J100.B7, U7.3, U7.4
/USB_DP: J9.3, J100.A6, J100.B6, U7.1, U7.6
GND: C30.2, J9.2, J100.A1, J100.A12, J100.B1, J100.B12, J100.SH, R20.2, R21.2, U7.2
unnamed: J100.A5, R20.1
unnamed: J100.B5, R21.1
USB_5V: C30.1, J9.1, J100.A4, J100.A9, J100.B4, J100.B9, U7.5

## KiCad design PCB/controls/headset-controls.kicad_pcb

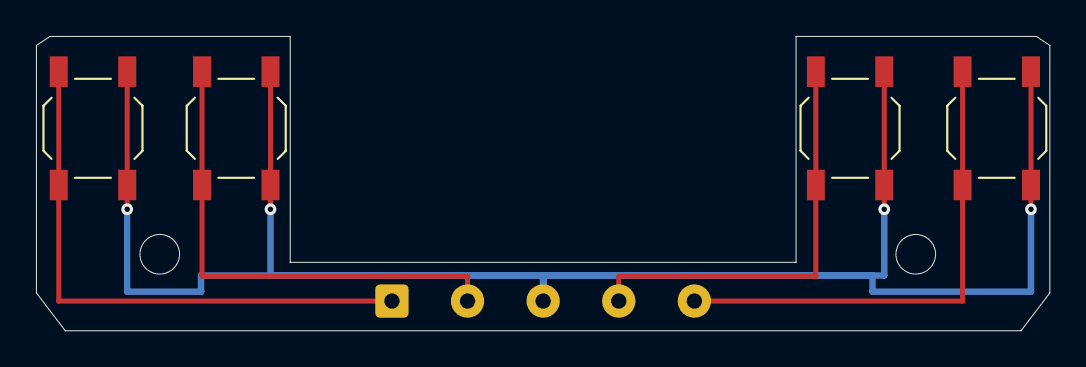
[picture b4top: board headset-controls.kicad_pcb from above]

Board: 2 copper layers, 56.3 x 16.4 mm, 7 parts (0 on the bottom side), 5 nets.

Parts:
H1, H2: 2.2 mm M2 clearance; MountingHole_2.2mm_M2
J1: Direct-wire harness; SolderWire-0.25sqmm_1x05_P4.2mm_D0.65mm_OD1.7mm
SW1, SW2, SW3, SW4: TL3342F260QG; SW_SPST_TL3342

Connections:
GND: J1.3, SW1.2, SW2.2, SW3.2, SW4.2
PAIR: J1.5, SW4.1
PLAY_PAUSE: J1.1, SW1.1
VOLUME_DOWN: J1.2, SW2.1
VOLUME_UP: J1.4, SW3.1

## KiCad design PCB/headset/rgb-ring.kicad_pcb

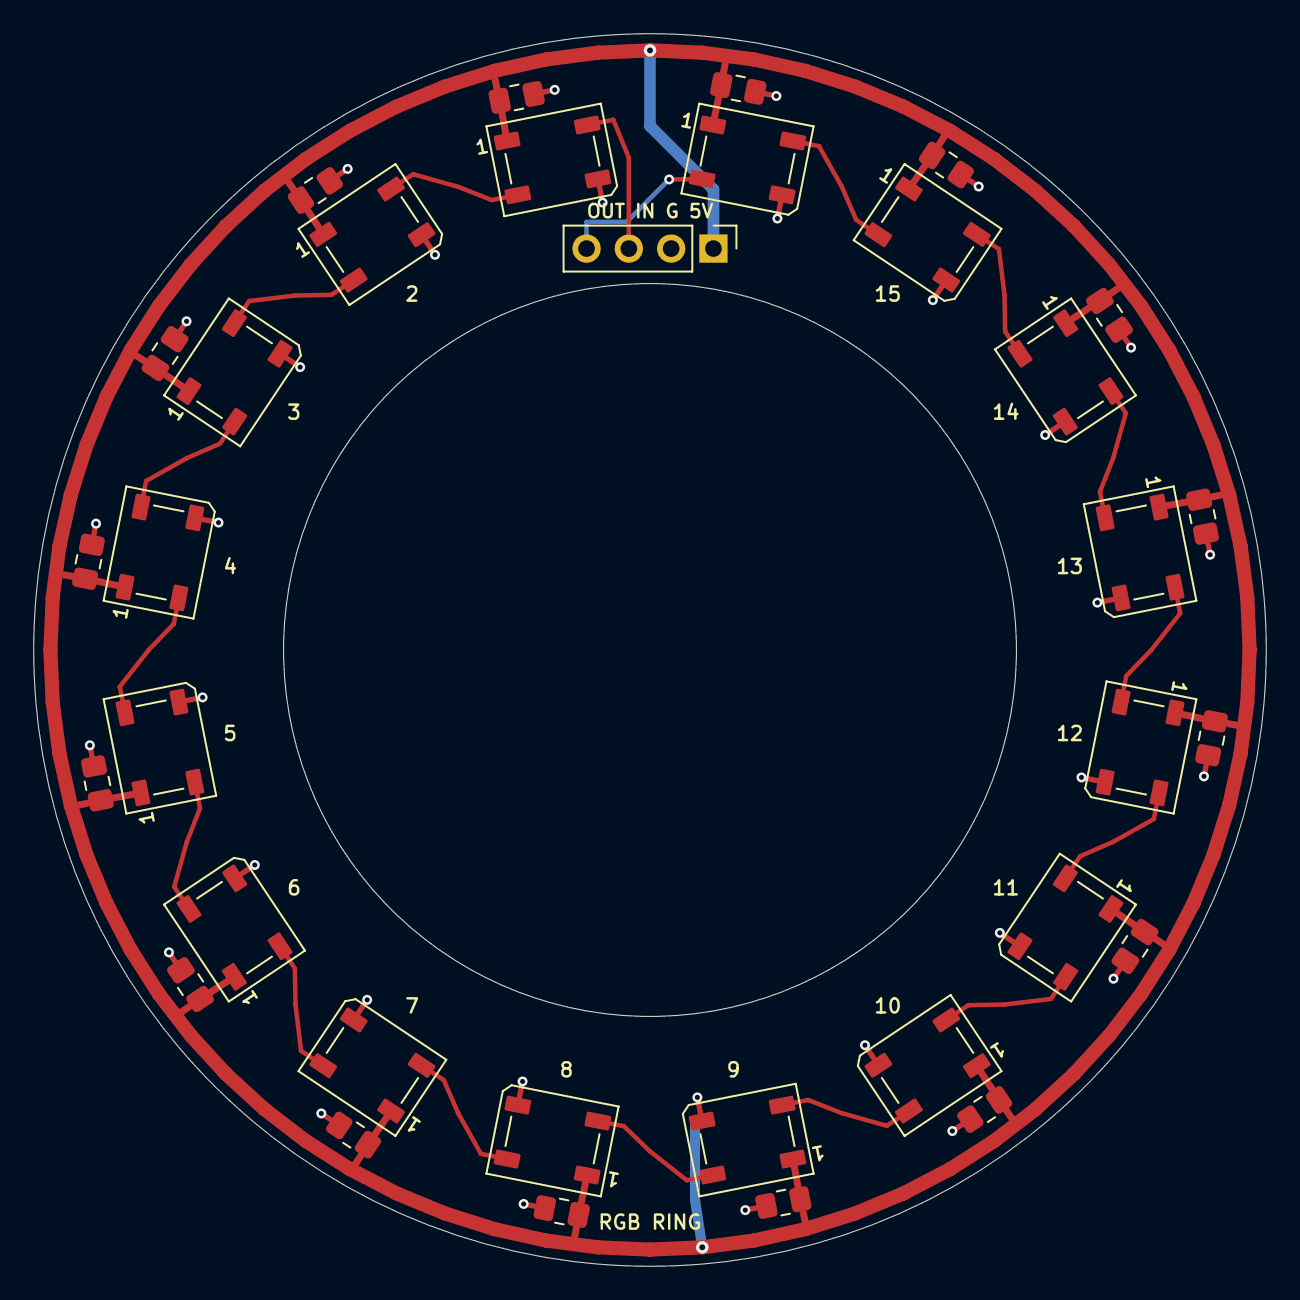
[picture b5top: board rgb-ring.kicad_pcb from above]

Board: 2 copper layers, 74.0 x 74.0 mm, 34 parts (1 on the bottom side), 19 nets.

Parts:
C36, C37, C38, C39, C40, C41, C42, C43, C44, C45, C46, C47, C48, C49, C50, C51: 100n; C_0805_2012Metric_Pad1.18x1.45mm_HandSolder
C52: 47u; CP_Elec_6.3x5.8
D1, D2, D3, D4, D5, D6, D7, D8, D9, D10, D11, D12, D13, D14, D15, D16: WS2812B; LED_WS2812B_PLCC4_5.0x5.0mm_P3.2mm
J12: Conn_01x04; PinHeader_1x04_P2.54mm_Vertical

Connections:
+5V_RGB: C36.1, C37.1, C38.1, C39.1, C40.1, C41.1, C42.1, C43.1, C44.1, C45.1, C46.1, C47.1, C48.1, C49.1, C50.1, C51.1, C52.1, D1.1, D2.1, D3.1, D4.1, D5.1, D6.1, D7.1, D8.1, D9.1, D10.1, D11.1, D12.1, D13.1, D14.1, D15.1, D16.1, J12.1
/RGB_LEFT_IN: D1.4, J12.3
/RGB_LEFT_OUT: D16.2, J12.4
GND: C36.2, C37.2, C38.2, C39.2, C40.2, C41.2, C42.2, C43.2, C44.2, C45.2, C46.2, C47.2, C48.2, C49.2, C50.2, C51.2, C52.2, D1.3, D2.3, D3.3, D4.3, D5.3, D6.3, D7.3, D8.3, D9.3, D10.3, D11.3, D12.3, D13.3, D14.3, D15.3, D16.3, J12.2
unnamed: D1.2, D2.4
unnamed: D2.2, D3.4
unnamed: D3.2, D4.4
unnamed: D4.2, D5.4
unnamed: D5.2, D6.4
unnamed: D6.2, D7.4
unnamed: D7.2, D8.4
unnamed: D8.2, D9.4
unnamed: D9.2, D10.4
unnamed: D10.2, D11.4
unnamed: D11.2, D12.4
unnamed: D12.2, D13.4
unnamed: D13.2, D14.4
unnamed: D14.2, D15.4
unnamed: D15.2, D16.4

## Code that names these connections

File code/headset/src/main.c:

#include <stdbool.h>
#include <stdint.h>

#include <zephyr/device.h>
#include <zephyr/drivers/gpio.h>
#include <zephyr/kernel.h>
#include <zephyr/sys/printk.h>

#include "bm83_link.h"
#include "audio_control.h"
#include "battery.h"
#include "codec.h"
#include "headset_logic.h"
#include "rgb.h"
#include "wireless_audio.h"

enum {
    PIN_MODE_N = 29,
    PIN_PAIR_N = 4,
    PIN_PLAY_N = 24,
    PIN_DOWN_N = 0,
    PIN_UP_N = 2,
    PIN_RGB_ENABLE = 22,
    PIN_BT_AUDIO_SEL = 31,
    PIN_CHG_N = 4,
    PIN_PGOOD_N = 5,
    PIN_BOOM_N = 11,
};

static const struct device *const gpio0 = DEVICE_DT_GET(DT_NODELABEL(gpio0));
static const struct device *const gpio1 = DEVICE_DT_GET(DT_NODELABEL(gpio1));

int main(void)
{
    struct headset_inputs inputs = {0};
    struct headset_input boom = {0};
    bool bluetooth_routed = false;
    int last_charger_status = -1;

    if (!device_is_ready(gpio0) || !device_is_ready(gpio1)) {
        printk("GPIO unavailable\n");
        return 1;
    }

    if (gpio_pin_configure(gpio0, PIN_RGB_ENABLE, GPIO_OUTPUT_INACTIVE) < 0 ||
        gpio_pin_configure(gpio0, PIN_BT_AUDIO_SEL, GPIO_OUTPUT_INACTIVE) < 0 ||
        gpio_pin_configure(gpio0, PIN_CHG_N, GPIO_INPUT) < 0 ||
        gpio_pin_configure(gpio0, PIN_PGOOD_N, GPIO_INPUT) < 0 ||
        gpio_pin_configure(gpio0, PIN_MODE_N, GPIO_INPUT) < 0 ||
        gpio_pin_configure(gpio1, PIN_BOOM_N, GPIO_INPUT | GPIO_PULL_UP) < 0 ||
        gpio_pin_configure(gpio1, PIN_PAIR_N, GPIO_INPUT | GPIO_PULL_UP) < 0 ||
        gpio_pin_configure(gpio0, PIN_PLAY_N, GPIO_INPUT | GPIO_PULL_UP) < 0 ||
        gpio_pin_configure(gpio1, PIN_DOWN_N, GPIO_INPUT | GPIO_PULL_UP) < 0 ||
        gpio_pin_configure(gpio1, PIN_UP_N, GPIO_INPUT | GPIO_PULL_UP) < 0) {
        printk("GPIO setup failed\n");
        return 1;
    }

    printk("Headset bring-up\n");
    const int battery_status = battery_start();
    if (battery_status < 0) {
        printk("Battery monitor unavailable: %d\n", battery_status);
    }
    const int codec_status = codec_prepare();
    printk("Codec clock register setup: %d\n", codec_status);
    const int bt_status = bm83_start();
    if (bt_status < 0) {
        printk("BM83 UART setup failed: %d\n", bt_status);
    }
    if (codec_status == 0) {
        const int wireless_status = wireless_audio_start();
        if (wireless_status < 0) {
            printk("Dongle audio setup failed: %d\n", wireless_status);
        }
    }
    const int rgb_status = rgb_start();
    if (rgb_status < 0) {
        printk("RGB over USB unavailable: %d\n", rgb_status);
    }

    for (;;) {
        const int mode = gpio_pin_get_raw(gpio0, PIN_MODE_N);
        const int pair = gpio_pin_get_raw(gpio1, PIN_PAIR_N);
        const int play = gpio_pin_get_raw(gpio0, PIN_PLAY_N);
        const int down = gpio_pin_get_raw(gpio1, PIN_DOWN_N);
        const int up = gpio_pin_get_raw(gpio1, PIN_UP_N);
        const int pgood = gpio_pin_get_raw(gpio0, PIN_PGOOD_N);
        const int charging = gpio_pin_get_raw(gpio0, PIN_CHG_N);

        if (mode < 0 || pair < 0 || play < 0 || down < 0 || up < 0) {
            printk("Input read failed\n");
            return 1;
        }

        const uint32_t now = k_uptime_get_32();
        const bool boom_muted = !headset_boom_deployed(&boom,
            gpio_pin_get_raw(gpio1, PIN_BOOM_N) == 0, now);
        bm83_set_mic_muted(boom_muted);
        wireless_audio_set_mic_muted(boom_muted);
        if (battery_status == 0) {
            battery_poll(now);
        }
        const uint8_t events = headset_inputs_update(&inputs, mode == 0, pair == 0, now);
        const bool play_pressed = headset_button_pressed(&inputs.play, play == 0, now);
        const bool down_pressed = headset_button_pressed(&inputs.volume_down, down == 0, now);
        const bool up_pressed = headset_button_pressed(&inputs.volume_up, up == 0, now);
        if (pgood >= 0 && charging >= 0) {
            const int charger_status = pgood != 0 ? 0 : (charging == 0 ? 2 : 1);
            if (charger_status != last_charger_status) {
                const char *const statuses[] = {"No valid input", "Input valid", "Charging"};
                printk("Charger: %s\n", statuses[charger_status]);
                last_charger_status = charger_status;
            }
        }

        if ((events & HEADSET_MODE_CHANGED) != 0U) {
            printk("Requested source: %s\n", inputs.mode_bluetooth.stable ?
                   "Bluetooth" : "USB dongle");
            if (bt_status == 0) {
                bm83_set_selected(inputs.mode_bluetooth.stable);
            }
            wireless_audio_select(!inputs.mode_bluetooth.stable);
        }
        if (!inputs.mode_bluetooth.stable) {
            if ((events & HEADSET_PAIR_PRESSED) != 0U) {
                wireless_audio_pair();
            }
            if (play_pressed) {
                wireless_audio_media(AUDIO_PLAY_PAUSE);
            }
            if (down_pressed) {
                wireless_audio_media(AUDIO_VOLUME_DOWN);
            }
            if (up_pressed) {
                wireless_audio_media(AUDIO_VOLUME_UP);
            }
        }
        if (bt_status == 0) {
            if ((events & HEADSET_PAIR_PRESSED) != 0U) {
                bm83_request_pairing();
            }
            if (play_pressed) {
                bm83_request_media(BM83_MEDIA_PLAY_PAUSE);
            }
            if (down_pressed) {
                bm83_request_media(BM83_MEDIA_VOLUME_DOWN);
            }
            if (up_pressed) {
                bm83_request_media(BM83_MEDIA_VOLUME_UP);
            }
            bm83_poll();
            const bool route_bluetooth = bm83_audio_available();
            if (route_bluetooth != bluetooth_routed) {
                if (gpio_pin_set(gpio0, PIN_BT_AUDIO_SEL, route_bluetooth) < 0) {
                    printk("Audio switch update failed\n");
                    return 1;
                }
                bluetooth_routed = route_bluetooth;
            }
        }

        rgb_poll(pgood <= 0);
        wireless_audio_poll();
        k_msleep(5);
    }
}
